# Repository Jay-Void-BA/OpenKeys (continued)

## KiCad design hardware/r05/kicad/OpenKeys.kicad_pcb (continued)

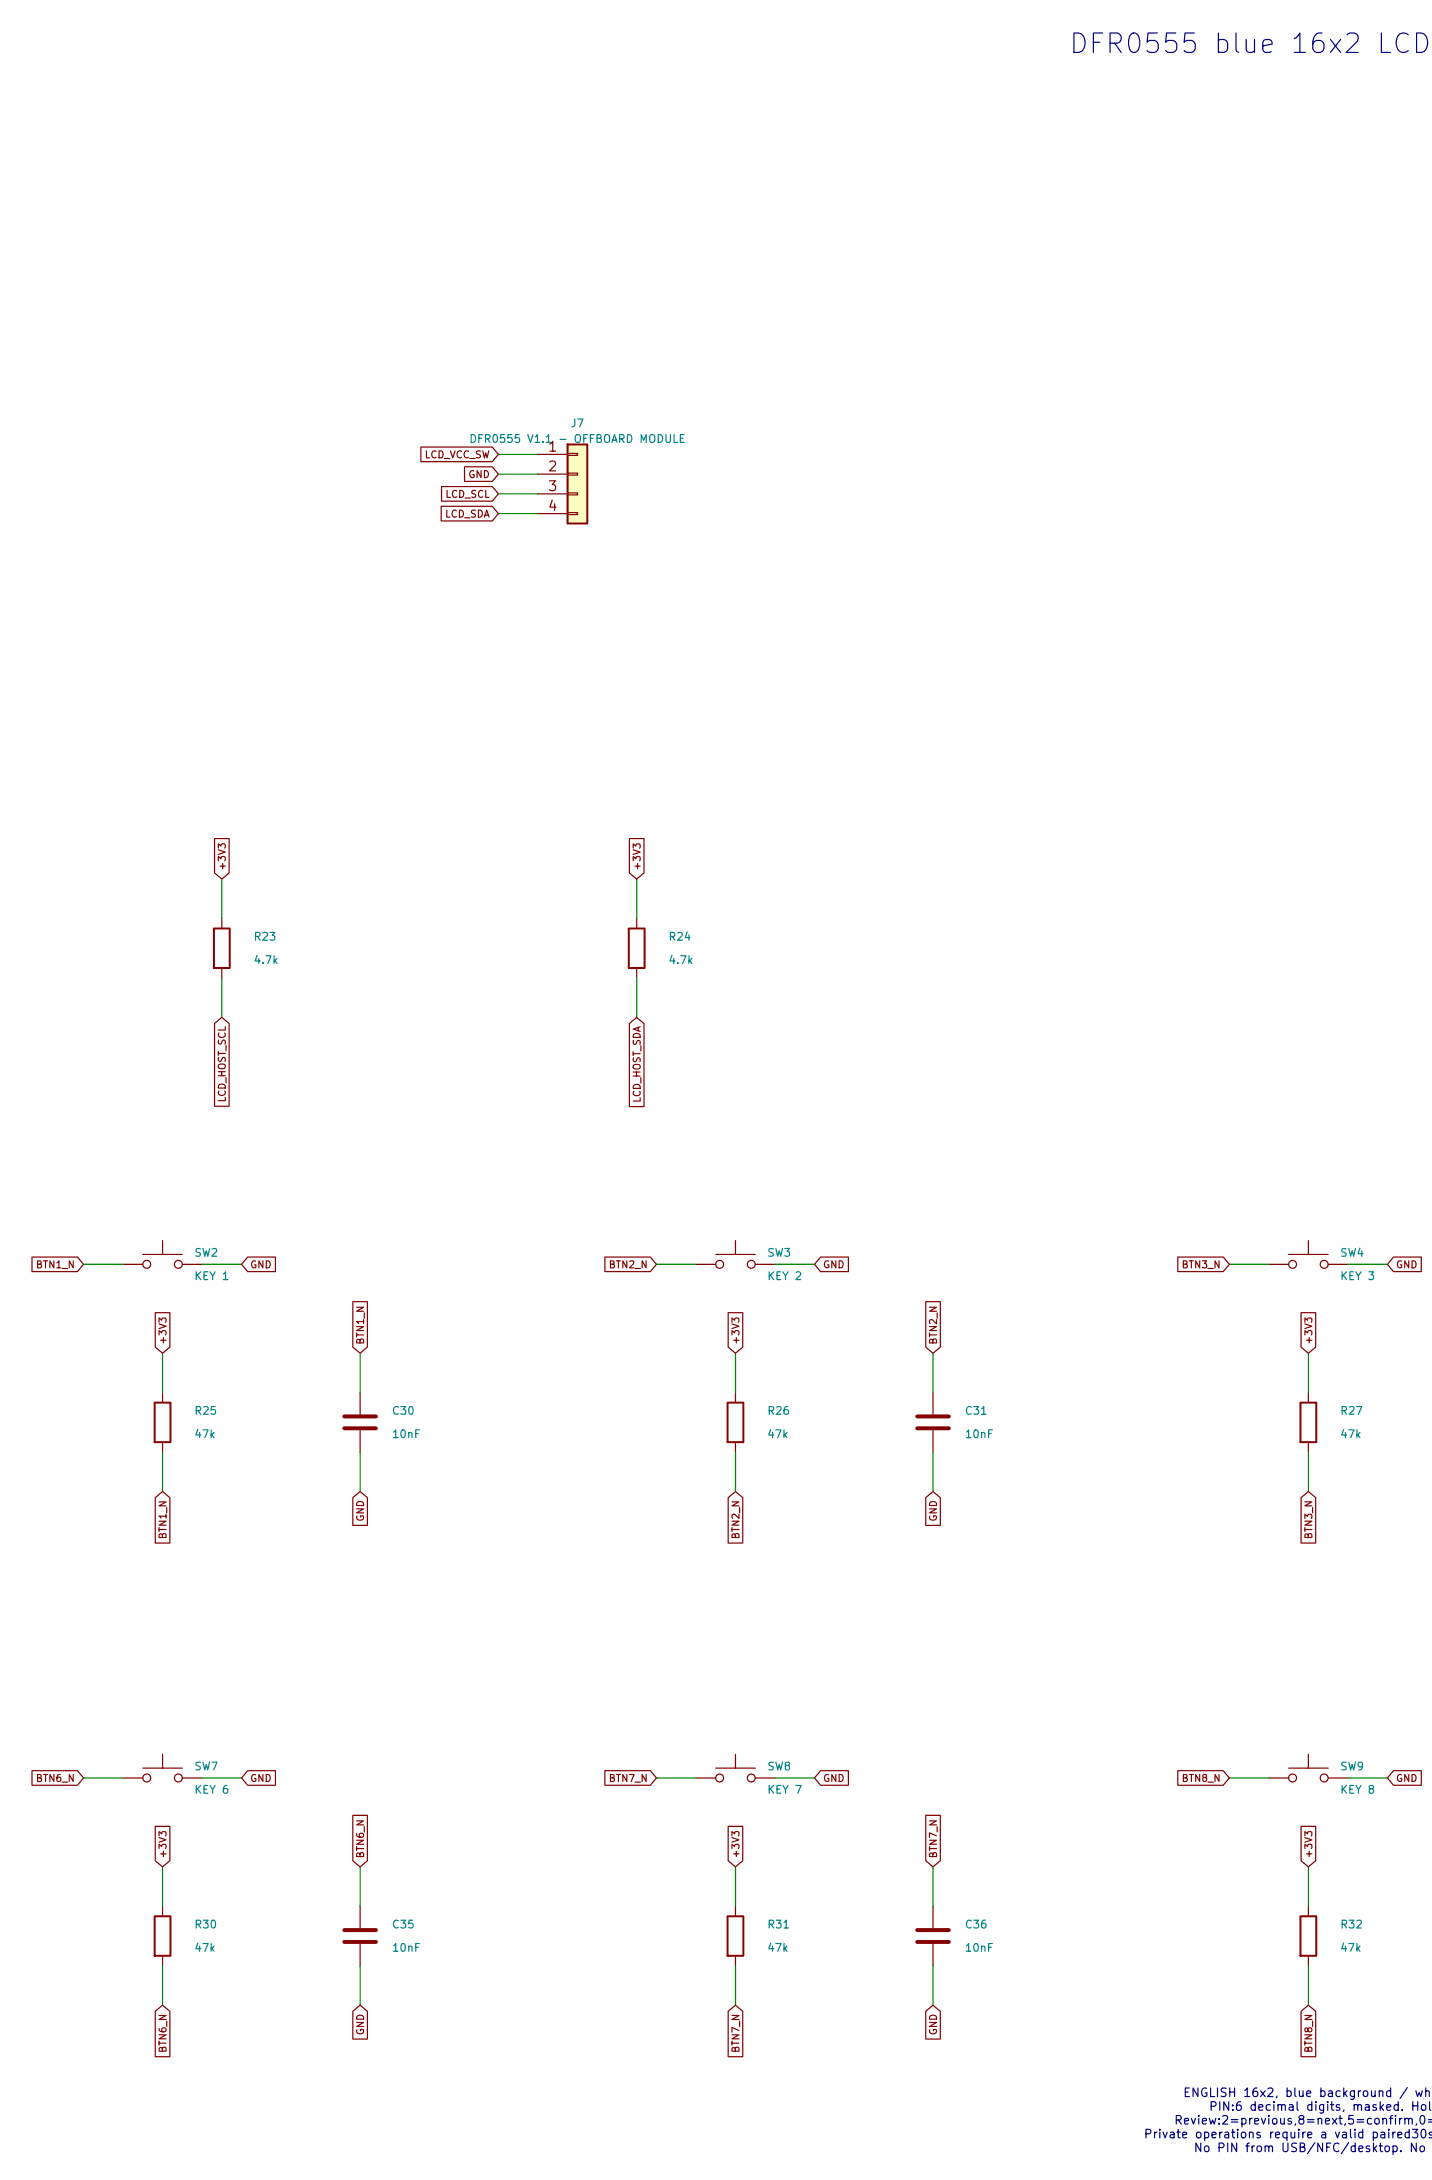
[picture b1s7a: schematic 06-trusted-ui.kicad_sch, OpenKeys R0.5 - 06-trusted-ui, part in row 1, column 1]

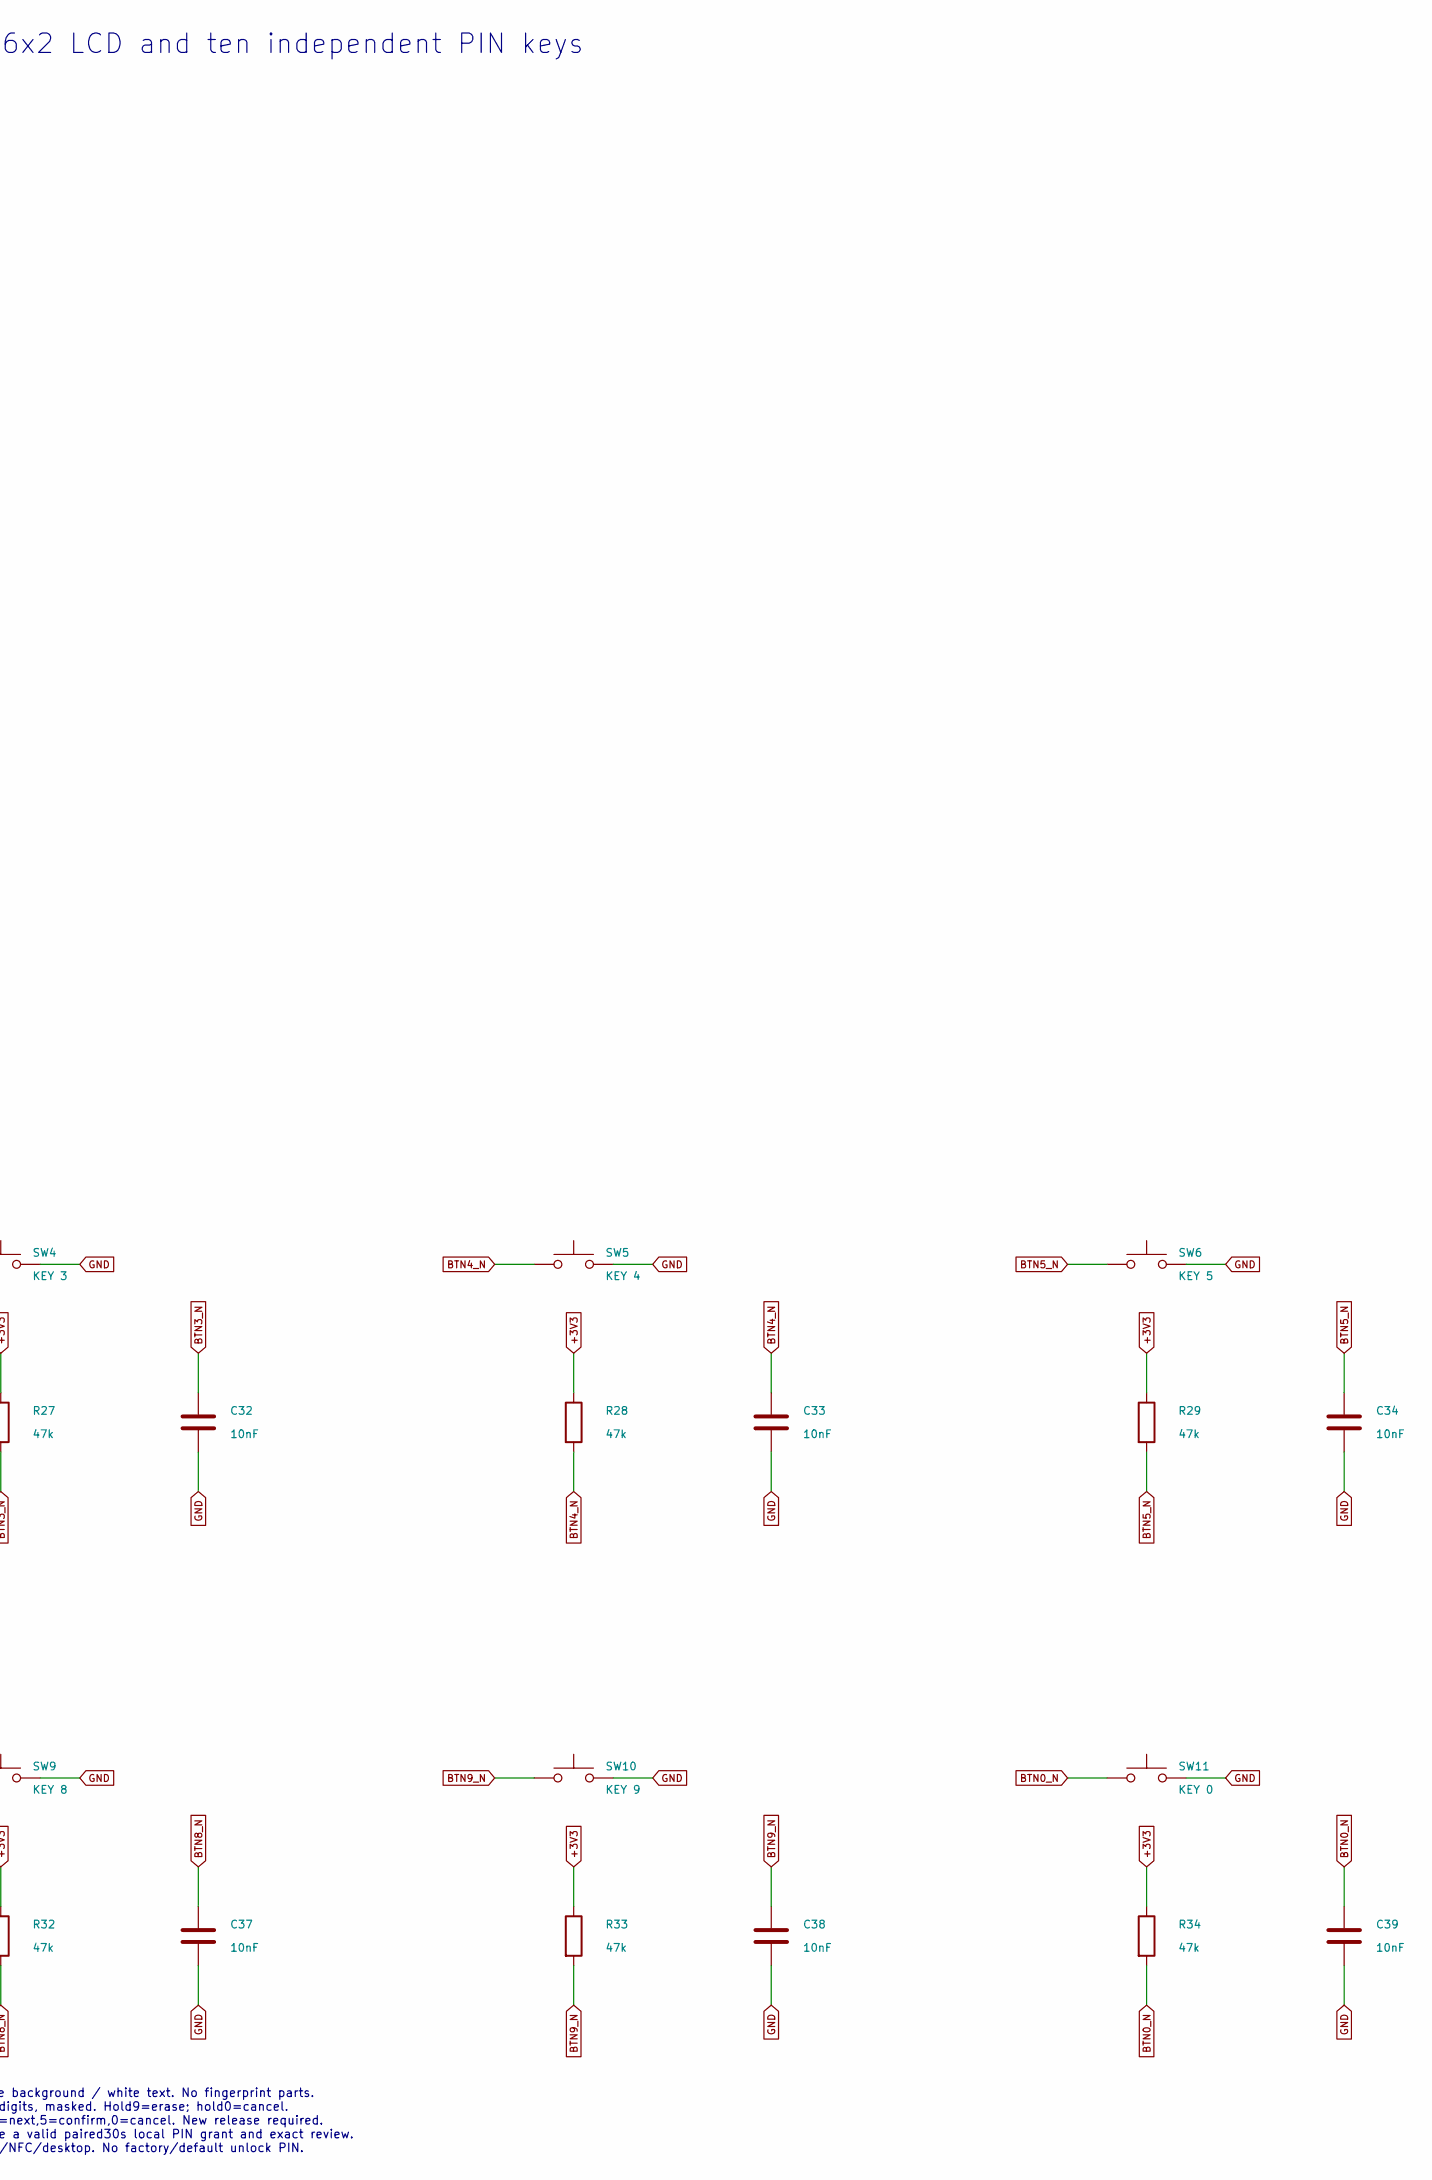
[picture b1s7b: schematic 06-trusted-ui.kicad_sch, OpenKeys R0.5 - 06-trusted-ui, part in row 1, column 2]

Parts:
C30, C31, C32, C33, C34, C35, C36, C37, C38, C39: 10nF; C_0603_1608Metric
J7: DFR0555 V1.1 - OFFBOARD MODULE; PinHeader_1x04_P2.54mm_Vertical
R23, R24: 4.7k; R_0603_1608Metric
R25, R26, R27, R28, R29, R30, R31, R32, R33, R34: 47k; R_0603_1608Metric
SW2: KEY 1; SW_SPST_TL3342
SW3: KEY 2; SW_SPST_TL3342
SW4: KEY 3; SW_SPST_TL3342
SW5: KEY 4; SW_SPST_TL3342
SW6: KEY 5; SW_SPST_TL3342
SW7: KEY 6; SW_SPST_TL3342
SW8: KEY 7; SW_SPST_TL3342
SW9: KEY 8; SW_SPST_TL3342
SW10: KEY 9; SW_SPST_TL3342
SW11: KEY 0; SW_SPST_TL3342

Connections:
+3V3: R23.1, R24.1, R25.1, R26.1, R27.1, R28.1, R29.1, R30.1, R31.1, R32.1, R33.1, R34.1; also elsewhere on the board
BTN0_N: C39.1, R34.2, SW11.1; also elsewhere on the board
BTN1_N: C30.1, R25.2, SW2.1; also elsewhere on the board
BTN2_N: C31.1, R26.2, SW3.1; also elsewhere on the board
BTN3_N: C32.1, R27.2, SW4.1; also elsewhere on the board
BTN4_N: C33.1, R28.2, SW5.1; also elsewhere on the board
BTN5_N: C34.1, R29.2, SW6.1; also elsewhere on the board
BTN6_N: C35.1, R30.2, SW7.1; also elsewhere on the board
BTN7_N: C36.1, R31.2, SW8.1; also elsewhere on the board
BTN8_N: C37.1, R32.2, SW9.1; also elsewhere on the board
BTN9_N: C38.1, R33.2, SW10.1; also elsewhere on the board
GND: C30.2, C31.2, C32.2, C33.2, C34.2, C35.2, C36.2, C37.2, C38.2, C39.2, J7.2, SW2.2, SW3.2, SW4.2, SW5.2, SW6.2, SW7.2, SW8.2, SW9.2, SW10.2, SW11.2; also elsewhere on the board
LCD_HOST_SCL: R23.2; also elsewhere on the board
LCD_HOST_SDA: R24.2; also elsewhere on the board
LCD_SCL: J7.3; also elsewhere on the board
LCD_SDA: J7.4; also elsewhere on the board
LCD_VCC_SW: J7.1; also elsewhere on the board

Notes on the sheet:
DFR0555 blue 16x2 LCD and ten independent PIN keys
ENGLISH 16x2, blue background / white text. No fingerprint parts. PIN:6 decimal digits, masked. Hold9=erase; hold0=cancel. Review:2=previous,8=next,5=confirm,0=cancel. New release required. Private operations require a valid paired30s local PIN grant and exact review. No PIN from USB/NFC/desktop. N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

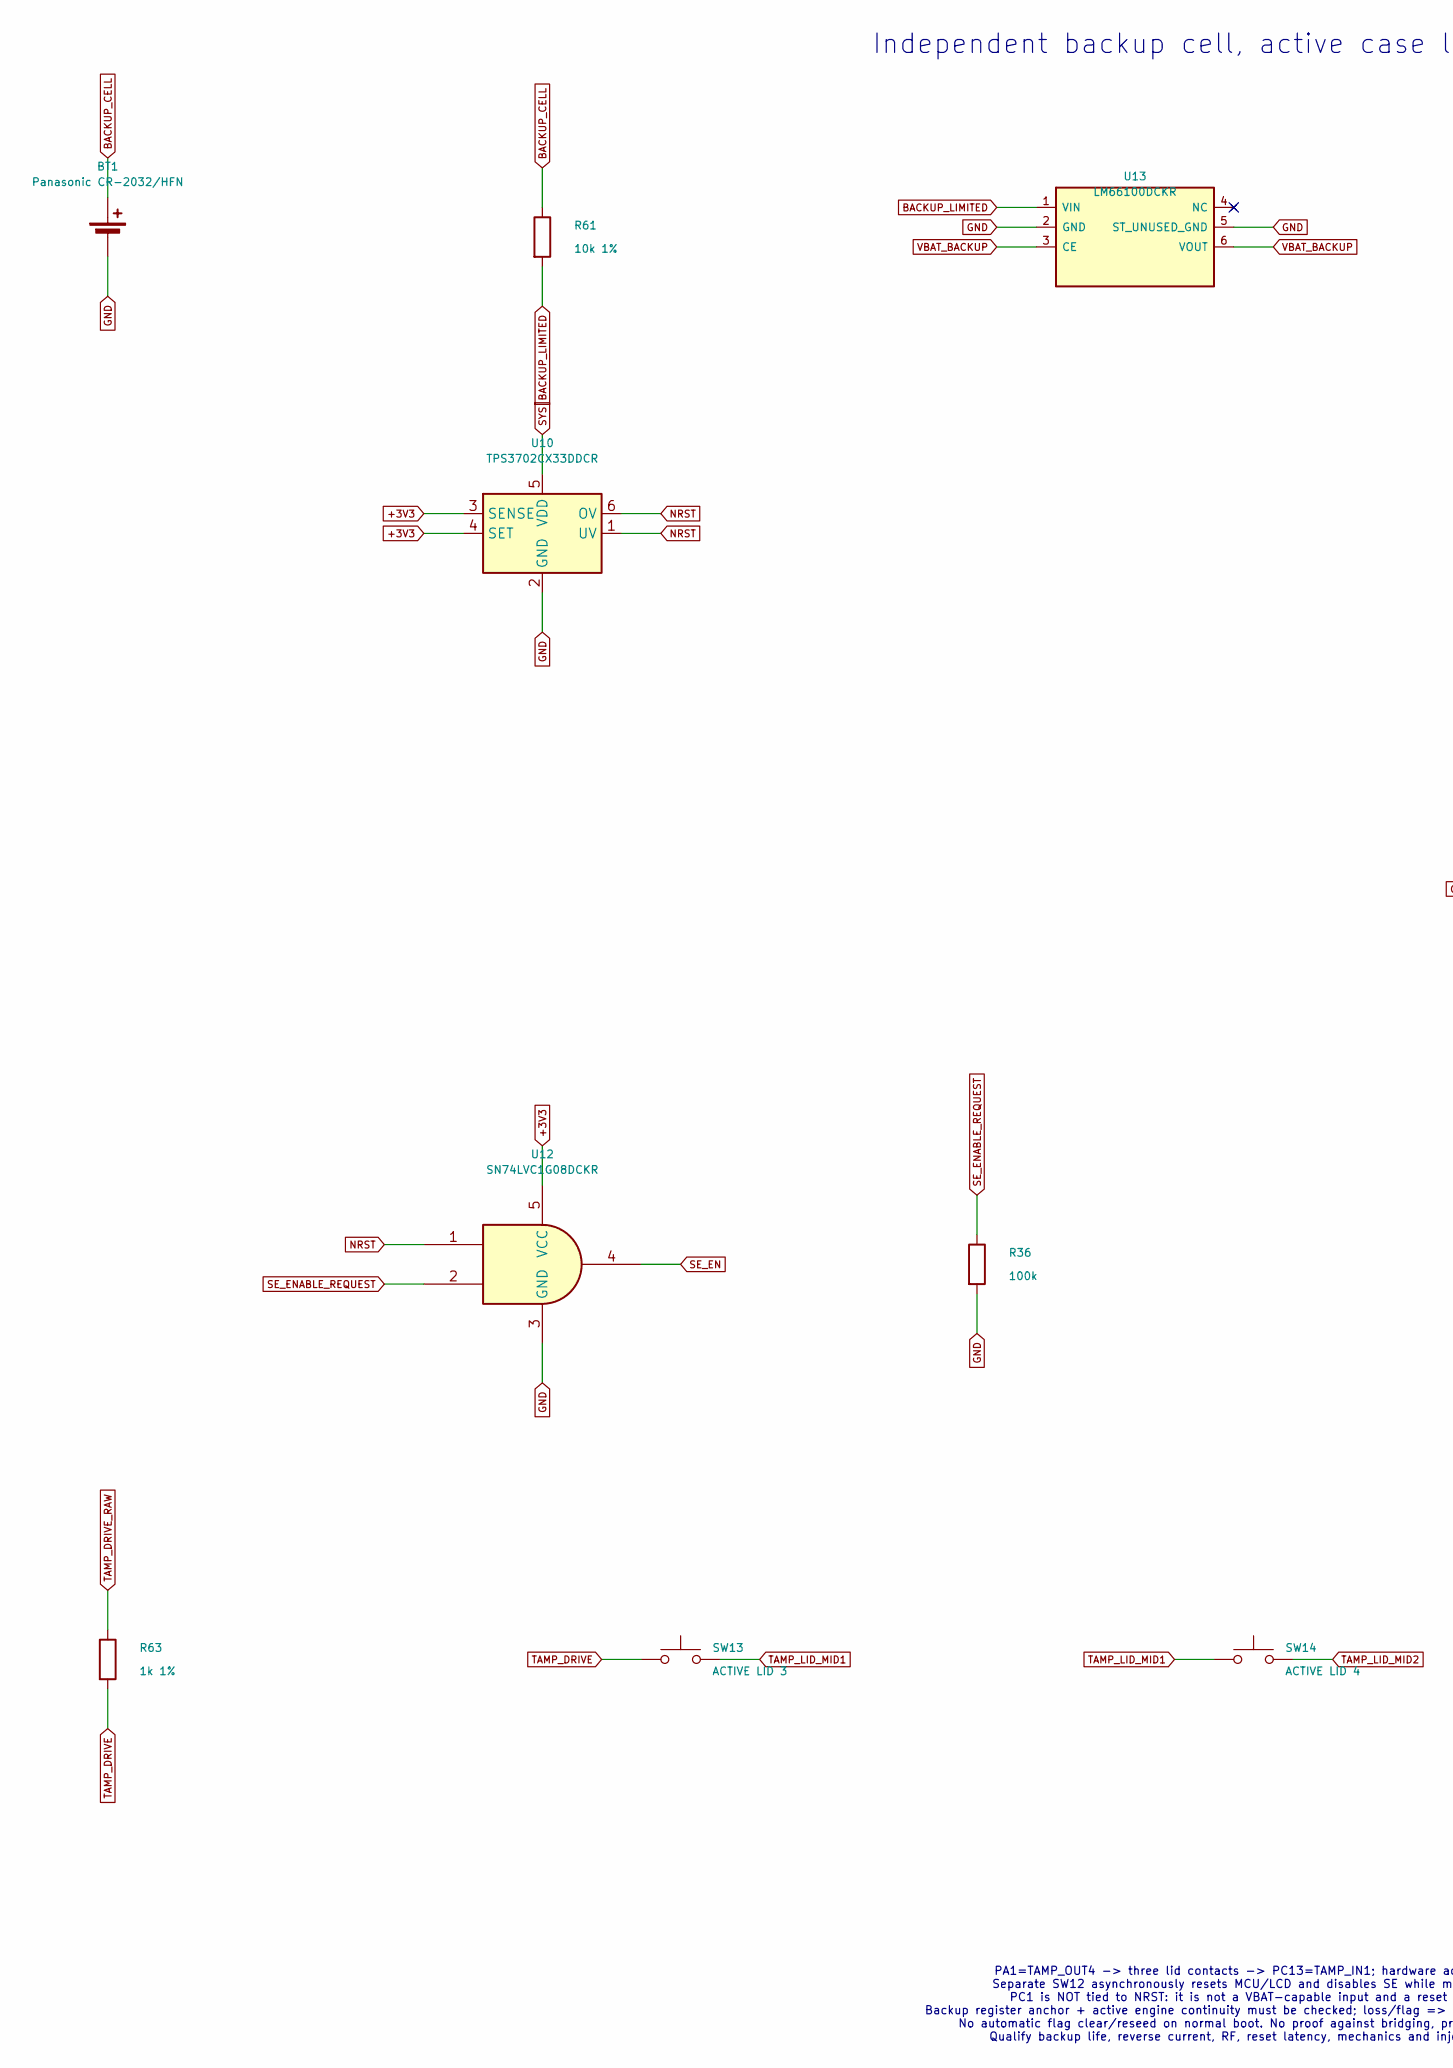
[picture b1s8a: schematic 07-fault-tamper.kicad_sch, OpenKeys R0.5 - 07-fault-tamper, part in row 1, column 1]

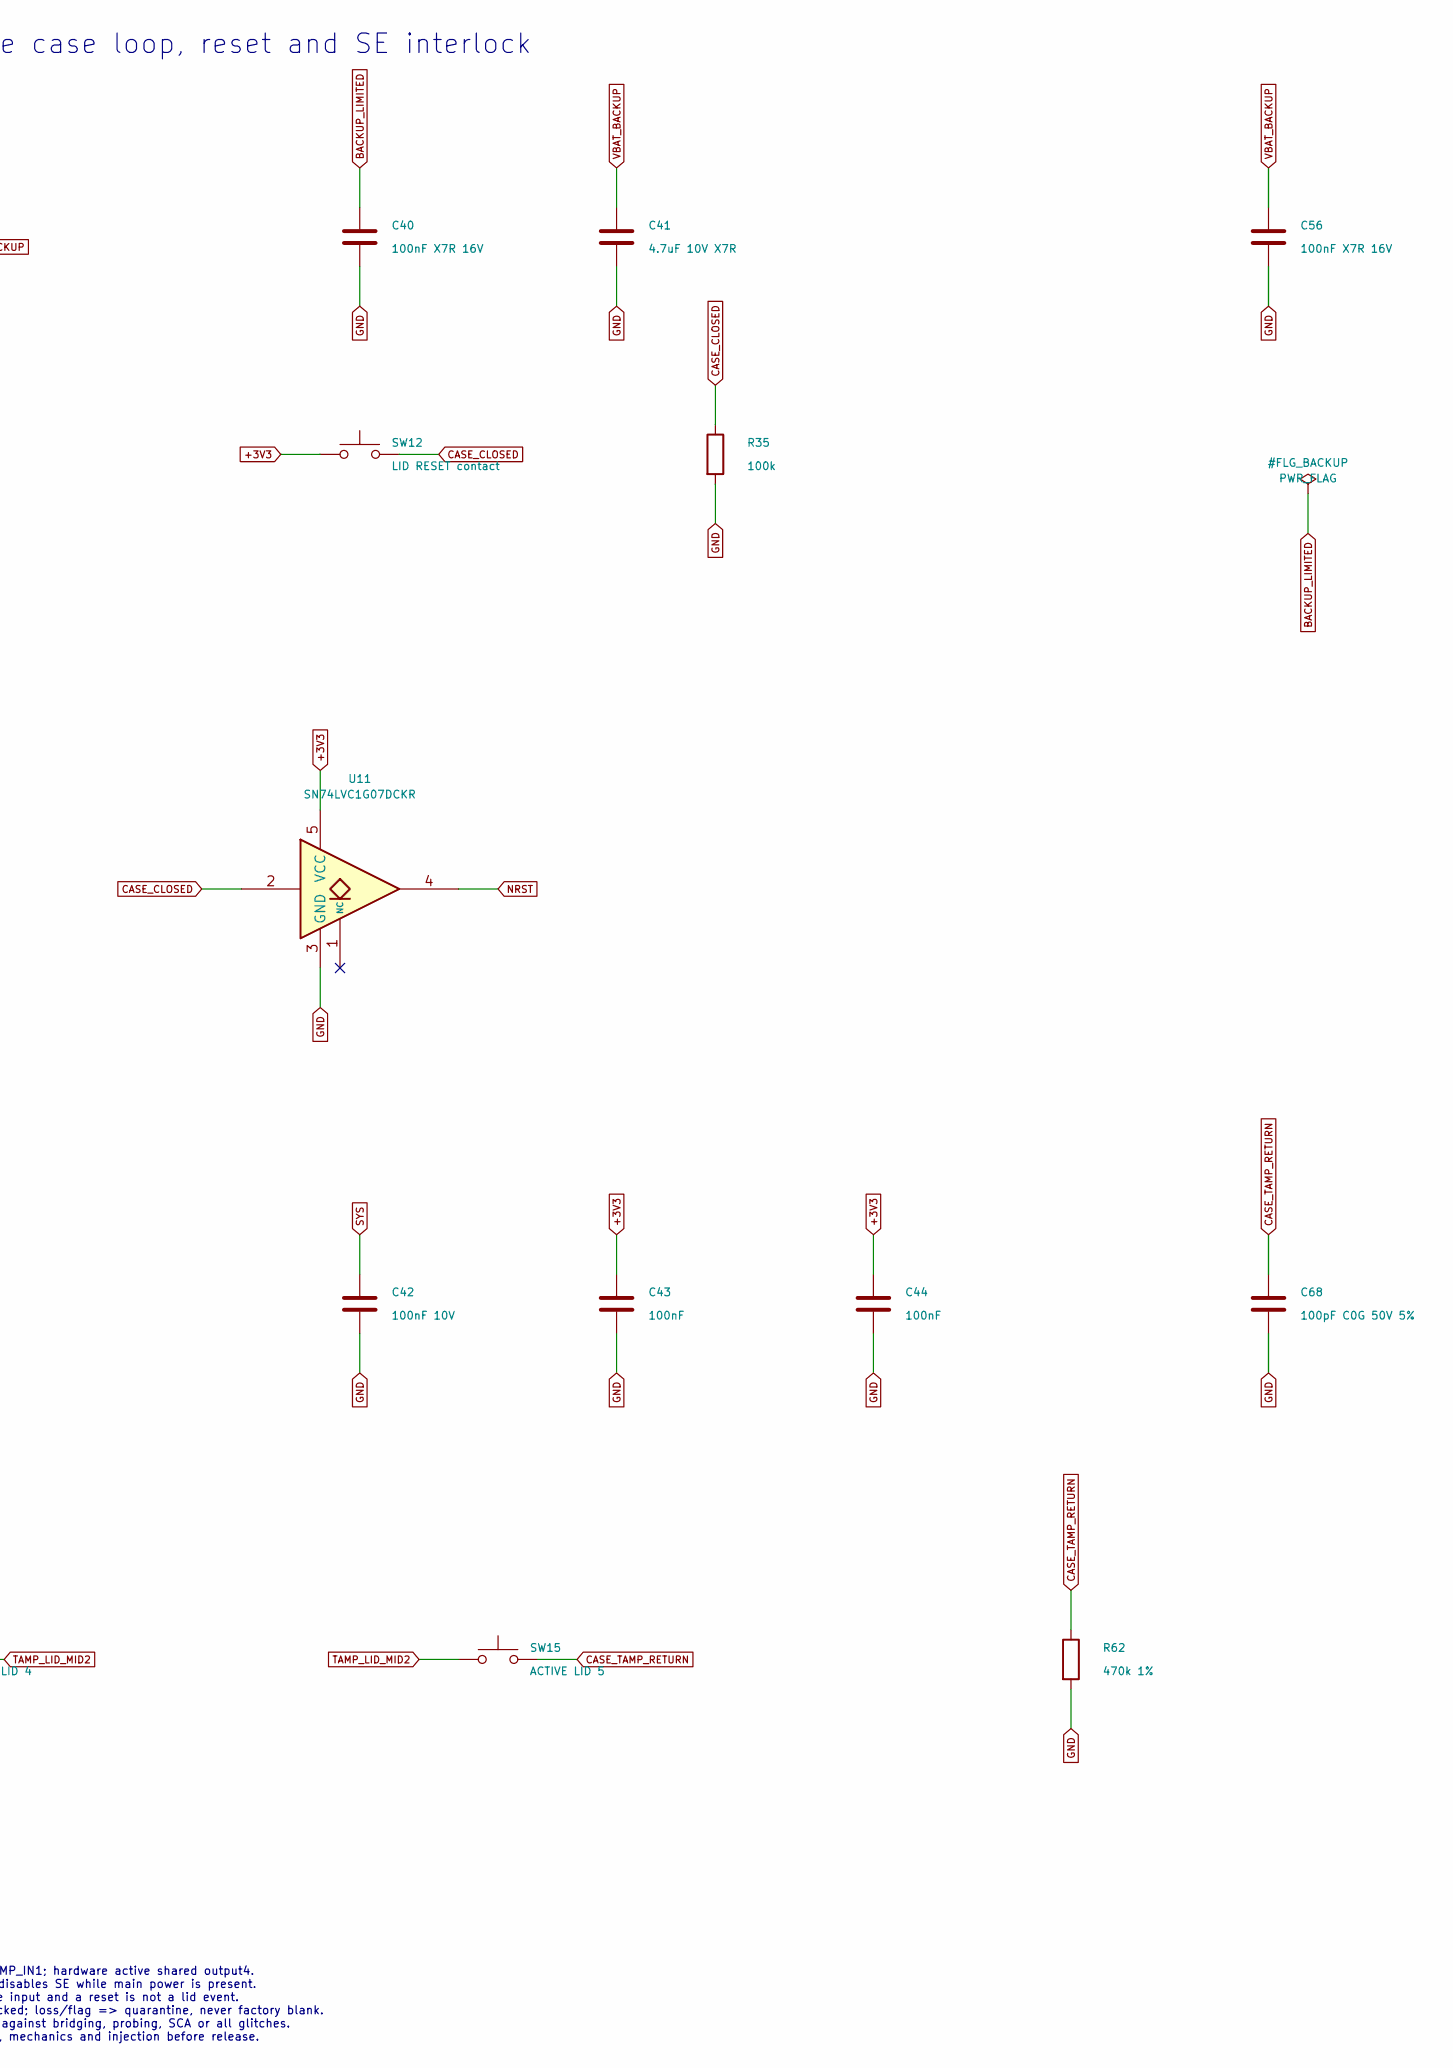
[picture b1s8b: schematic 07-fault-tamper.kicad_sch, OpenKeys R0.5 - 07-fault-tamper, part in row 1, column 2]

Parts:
BT1: Panasonic CR-2032/HFN; Battery_Panasonic_CR2032-HFN_Horizontal_CircularHoles
C40, C56: 100nF X7R 16V; C_0603_1608Metric
C41: 4.7uF 10V X7R; C_0805_2012Metric
C42: 100nF 10V; C_0603_1608Metric
C43, C44: 100nF; C_0603_1608Metric
C68: 100pF C0G 50V 5%; C_0603_1608Metric
R35, R36: 100k; R_0603_1608Metric
R61: 10k 1%; R_0603_1608Metric
R62: 470k 1%; R_0603_1608Metric
R63: 1k 1%; R_0603_1608Metric
SW12: LID RESET contact; SW_SPST_TL3342
SW13: ACTIVE LID 3; SW_SPST_TL3342
SW14: ACTIVE LID 4; SW_SPST_TL3342
SW15: ACTIVE LID 5; SW_SPST_TL3342
U10: TPS3702CX33DDCR; TSOT-23-6
U11: SN74LVC1G07DCKR; SOT-353_SC-70-5
U12: SN74LVC1G08DCKR; SOT-353_SC-70-5
U13: LM66100DCKR; SOT-363_SC-70-6

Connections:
+3V3: C43.1, C44.1, SW12.1, U10.3 (SENSE), U10.4 (SET), U11.5 (VCC), U12.5 (VCC); also elsewhere on the board
BACKUP_CELL: BT1.1 (+), R61.1
BACKUP_LIMITED: C40.1, R61.2, U13.1 (VIN)
CASE_CLOSED: R35.1, SW12.2, U11.2
CASE_TAMP_RETURN: C68.1, R62.1, SW15.2; also elsewhere on the board
GND: BT1.2 (-), C40.2, C41.2, C42.2, C43.2, C44.2, C56.2, C68.2, R35.2, R36.2, R62.2, U10.2 (GND), U11.3 (GND), U12.3 (GND), U13.2 (GND), U13.5 (ST_UNUSED_GND); also elsewhere on the board
NRST: U10.1 (UV), U10.6 (OV), U11.4, U12.1; also elsewhere on the board
SE_EN: U12.4; also elsewhere on the board
SE_ENABLE_REQUEST: R36.1, U12.2; also elsewhere on the board
SYS: C42.1, U10.5 (VDD); also elsewhere on the board
TAMP_DRIVE: R63.2, SW13.1
TAMP_DRIVE_RAW: R63.1; also elsewhere on the board
TAMP_LID_MID1: SW13.2, SW14.1
TAMP_LID_MID2: SW14.2, SW15.1
VBAT_BACKUP: C41.1, C56.1, U13.3 (CE), U13.6 (VOUT); also elsewhere on the board

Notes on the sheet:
Independent backup cell, active case loop, reset and SE interlock
PA1=TAMP_OUT4 -> three lid contacts -> PC13=TAMP_IN1; hardware active shared output4. Separate SW12 asynchronously resets MCU/LCD and disables SE while main power is present. PC1 is NOT tied to NRST: it is not a VBAT-capable input and a reset is not a lid event. Backup register anchor + active engi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

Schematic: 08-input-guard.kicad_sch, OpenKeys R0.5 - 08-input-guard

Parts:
C45: 100nF 50V; C_0603_1608Metric
C46: 1nF C0G; C_0603_1608Metric
D4: BZT52-C5V1,115; D_SOD-123
D5: SMF16A; D_SOD-123F
R37: 22.1k 1%; R_0603_1608Metric
R38: 10k 1%; R_0603_1608Metric
R39: 374k 0.1%; R_0603_1608Metric
R40: 100k 0.1%; R_0603_1608Metric
R41: 6.49k 1%; R_0603_1608Metric
R42: 47k; R_0603_1608Metric
U14: TPS259470LRPWR; TPS25947_RPW0010A

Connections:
+3V3: R42.1; also elsewhere on the board
GND: C45.2, C46.2, D4.2 (A), D5.2 (A2), R38.2, R40.2, R41.2, U14.8 (GND); also elsewhere on the board
USB_5V: U14.6 (OUT); also elsewhere on the board
USB_GUARD_DVDT: C46.1, U14.7 (DVDT)
USB_GUARD_EN: D4.1 (K), R37.2, R38.1, U14.1 (EN_UVLO)
USB_GUARD_FAULT_N: R42.2, U14.4 (FLT_N); also elsewhere on the board
USB_GUARD_ILM: R41.1, U14.9 (ILM)
USB_GUARD_OV: R39.2, R40.1, U14.2 (OVLO)
VBUS_FUSED: C45.1, D5.1 (A1), R37.1, R39.1, U14.5 (IN); also elsewhere on the board

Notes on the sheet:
Independent VBUS overvoltage cutoff, reverse blocking and limited inrush
OVLO nominal1.2V x(1+374k/100k)=5.688V. Component/leakage corners in protection-calculations.json. UVLO divider22.1k/10k: about3.85V nominal. EN is separately clamped, never raw VBUS. 6.49k ILM: about0.51A protection threshold; BQ charger still sets100mA input budget. 1nF DVDT: about2V/ms, about2.5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

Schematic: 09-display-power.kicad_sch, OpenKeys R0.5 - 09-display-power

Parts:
C47, C51, C52, C53, C54, C55: 100nF; C_0603_1608Metric
C48: 100nF 10% X7R 16V; C_0603_1608Metric
C49, C50: 1uF 10V; C_0805_2012Metric
R43: 10k; R_0603_1608Metric
R44, R45, R48: 100k; R_0603_1608Metric
R46: 220k 1%; R_0603_1608Metric
R47: 330R 1% 0.25W; R_1206_3216Metric
U15: SN74LVC1G07DCKR; SOT-353_SC-70-5
U16: SN74LVC1G74DCUR; VSSOP-8_2.3x2mm_P0.5mm
U17: TPS3808G33DBVR; SOT-23-6
U18: TPS22919DCKR; SOT-363_SC-70-6
U19: SN74LVC1G17DCKR; SOT-353_SC-70-5
U20: SN74LVC1G08DCKR; SOT-353_SC-70-5
U21: TCA9517ADGKR; VSSOP-8_3x3mm_P0.65mm

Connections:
+3V3: C47.1, C51.1, C52.1, C53.1, C54.1, C55.1, R43.1, U15.5 (VCC), U16.2 (D), U16.7 (PRE_N), U16.8 (VCC), U17.5 (SENSE), U17.6 (VDD), U19.5 (VCC), U20.5 (VCC), U21.1 (VCCA); also elsewhere on the board
BUS_ENABLE: R48.1, U20.4; also elsewhere on the board
CLEAR_N: U16.6 (CLR_N), U17.1 (RESET_N); also elsewhere on the board
CONNECT_DELAY: C48.1, R46.2, U19.2
DELAY_READY: U19.4, U20.2
GND: C47.2, C48.2, C49.2, C50.2, C51.2, C52.2, C53.2, C54.2, C55.2, R44.2, R45.2, R47.2, R48.2, U15.3 (GND), U16.4 (GND), U17.2 (GND), U18.2 (GND), U19.3 (GND), U20.3 (GND), U21.4 (GND); also elsewhere on the board
LCD_ARM_CLK: R45.1, U16.1 (CLK); also elsewhere on the board
LCD_BUFFER_EN: U21.5 (EN); also elsewhere on the board
LCD_HOST_SCL: U21.2 (SCLA); also elsewhere on the board
LCD_HOST_SDA: U21.3 (SDAA); also elsewhere on the board
LCD_RELEASE: R43.2, R44.1, U15.4, U17.3 (MR_N); also elsewhere on the board
LCD_RESET_CT: U17.4 (CT); also elsewhere on the board
LCD_SCL: U21.7 (SCLB); also elsewhere on the board
LCD_SDA: U21.6 (SDAB); also elsewhere on the board
LCD_VCC_SW: C50.1, R47.1, U18.5 (QOD), U18.6 (OUT), U21.8 (VCCB); also elsewhere on the board
NRST: U15.2; also elsewhere on the board
POWER_LATCH: R46.1, U16.5 (Q), U18.3 (ON), U20.1; also elsewhere on the board
SYS: C49.1, U18.1 (IN); also elsewhere on the board

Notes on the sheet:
Latched LCD power removal; isolated bus; no resetless retained text
U16 D=1, PRE_N=1. NRST/PC3 low clears Q through U17. CT through100k to VDD: RESET_N stays low180..420ms after MR release. Reset release alone does not restore LCD power; a NEW PC4 edge is required. Q controls TPS22919; Q AND delayed-Q drives U21 EN through U23 on sheet10. Lock: PC4 low, PC3 low, wa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

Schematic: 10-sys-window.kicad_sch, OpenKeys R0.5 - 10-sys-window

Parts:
C57, C58, C59: 100nF; C_0603_1608Metric
C60: 100nF X7R 16V 10%; C_0603_1608Metric
R49: 78.7k 0.1%; R_0603_1608Metric
R50, R52: 10k 0.1%; R_0603_1608Metric
R51: 110k 0.1%; R_0603_1608Metric
R53, R57, R59: 10k 1%; R_0603_1608Metric
R54, R58: 100k 1%; R_0603_1608Metric
R55, R56: 4.7k; R_0603_1608Metric
U22: TPS3700DDCR; TSOT-23-6
U23: SN74LVC1G07DCKR; SOT-353_SC-70-5

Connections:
+3V3: C58.1, C59.1, C60.1, R57.1, R58.1, U22.5 (VDD), U23.5 (VCC); also elsewhere on the board
BUS_ENABLE: U23.2; also elsewhere on the board
CLEAR_N: R57.2; also elsewhere on the board
GND: C57.2, C58.2, C59.2, C60.2, R50.2, R52.2, R54.2, R59.2, U22.2 (GND), U23.3 (GND); also elsewhere on the board
LCD_BUFFER_EN: R53.2, R54.1, U23.4; also elsewhere on the board
LCD_RESET_CT: R58.2; also elsewhere on the board
LCD_SCL: R55.2; also elsewhere on the board
LCD_SDA: R56.2; also elsewhere on the board
LCD_VCC_SW: C57.1, R53.1, R55.1, R56.1; also elsewhere on the board
NRST: U22.1 (OUTA), U22.6 (OUTB); also elsewhere on the board
POWER_LATCH: R59.1; also elsewhere on the board
SYS: R49.1, R51.1; also elsewhere on the board
SYS_OV_SENSE: R51.2, R52.1, U22.4 (INB-)
SYS_UV_SENSE: R49.2, R50.1, U22.3 (INA+)

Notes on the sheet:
SYS voltage window and LCD level-buffer fail-closed enable
TPS3700 reference: positive396..404mV; negative387..400mV. Include0.1percent divider errors and +/-25nA input bias. Static SYS UV fall min3.4246V; OV rise max4.8596V. With ASSUMED switch+harness drop<=50mV: LCD>=3.3746V. Main3.3V fixed PWM:3.267..3.333V; no ripple/transient guarantee. TCA sideA=mai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

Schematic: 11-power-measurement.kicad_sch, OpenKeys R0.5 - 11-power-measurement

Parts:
C61: 10nF X7R 16V; C_0603_1608Metric
C67: 100nF X7R 16V; C_0603_1608Metric
R64, R65: 330k 1%; R_0603_1608Metric
R68: 100k 1%; R_0603_1608Metric
U28: TMUX1511RWBR; Texas_X2QFN-12_1.6x1.6mm_P0.4mm

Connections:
+3V3: C67.1, U28.2 (VDD); also elsewhere on the board
BAT: R64.1; also elsewhere on the board
BATTERY_DIVIDER: C61.1, R64.2, R65.1, U28.3 (S1)
BATTERY_SENSE: R68.1, U28.4 (D1); also elsewhere on the board
GND: C61.2, C67.2, R65.2, R68.2, U28.1 (GND), U28.5 (S2), U28.6 (D2), U28.8 (SEL2), U28.9 (D4), U28.10 (S4), U28.11 (D3), U28.12 (S3); also elsewhere on the board
NRST: U28.7 (SEL1); also elsewhere on the board

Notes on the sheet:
Protected main-cell voltage measurement; no invented battery percentage
PA0=ADC1_INP0 analog only. Read VREFINT/calibration; use long sample time and settled bounded samples. 330k/330k divider +100k output bias: nominal Vadc/Vbat=100/530 when U28 is on. Reservoir is upstream of U28. NRST low disconnects ADC; powered-off path must not backfeed main rail. Voltage/chargin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

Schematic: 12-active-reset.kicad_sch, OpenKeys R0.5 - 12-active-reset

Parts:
C62: 10nF X7R 16V 10%; C_0603_1608Metric
C63, C64, C65, C66: 100nF X7R 16V; C_0603_1608Metric
R66: 4.7k 1%; R_0603_1608Metric
R67: 1M 1%; R_0603_1608Metric
R69: 9.1k 1%; R_0603_1608Metric
U24: SN74AUP1G99DCUR; VSSOP-8_2.3x2mm_P0.5mm
U25: SN74LVC1G14DCKR; SOT-353_SC-70-5
U26: SN74LVC1G07DCKR; SOT-353_SC-70-5
U27: SN74AUP2G17DCKR; SOT-363_SC-70-6

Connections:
+3V3: C63.1, C64.1, C65.1, C66.1, R69.1, U24.3 (B), U24.8 (VCC), U25.5 (VCC), U26.5 (VCC), U27.5 (VCC); also elsewhere on the board
CASE_TAMP_RETURN: U27.3 (2A); also elsewhere on the board
GND: C62.2, C63.2, C64.2, C65.2, C66.2, R67.2, R69.2, U24.1 (OE_N), U24.2 (A), U24.4 (GND), U25.3 (GND), U26.3 (GND), U27.2 (GND); also elsewhere on the board
NRST: U26.4; also elsewhere on the board
TAMP_DIFF: R66.1, U24.7 (Y)
TAMP_DIFF_FILTER: C62.1, R66.2, U25.2
TAMP_DRIVE_CLEAN: U24.5 (C), U27.6 (1Y)
TAMP_DRIVE_RAW: R67.1, U27.1 (1A); also elsewhere on the board
TAMP_MATCH_N: U25.4, U26.2
TAMP_RETURN_CLEAN: U24.6 (D), U27.4 (2Y)

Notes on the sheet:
Independent active-loop mismatch reset; no software arm or override
Closed loop: C=D => no reset. Open/stuck/grounded loop: mismatch pulses feed RC and hard reset. U24 OE and function straps are fixed copper, not GPIO. No host bypass or software mask. U27 Ioff limits feed into unpowered main logic; leakage is not zero. No maximum input slew at U27/U25. Active TAMP 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

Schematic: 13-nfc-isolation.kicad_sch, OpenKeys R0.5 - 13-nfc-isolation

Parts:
C69, C70, C71: 100nF X7R 16V; C_0603_1608Metric
R70, R71, R72, R73, R74: 330R 1%; R_0603_1608Metric
R75, R76, R77: 100k 1%; R_0603_1608Metric
U29, U30: TMUX1511RWBR; Texas_X2QFN-12_1.6x1.6mm_P0.4mm
U31: LM66100DCKR; SOT-363_SC-70-6

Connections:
+3V3: C69.1, C70.1, C71.1, U29.2 (VDD), U30.2 (VDD), U31.1 (VIN); also elsewhere on the board
GND: C69.2, C70.2, C71.2, R76.2, R77.2, U29.1 (GND), U30.1 (GND), U30.5 (S2), U30.6 (D2), U30.9 (D4), U30.10 (S4), U30.11 (D3), U30.12 (S3), U31.2 (GND), U31.5 (ST_UNUSED_GND); also elsewhere on the board
NFC_CS_ISO: R70.1, U29.4 (D1)
NFC_CS_N: U29.3 (S1); also elsewhere on the board
NFC_IRQ_ISO: R74.1, U30.4 (D1)
NFC_IRQ_N: U30.3 (S1); also elsewhere on the board
NFC_MISO: U29.10 (S4); also elsewhere on the board
NFC_MISO_ISO: R73.1, U29.9 (D4)
NFC_MOSI: U29.12 (S3); also elsewhere on the board
NFC_MOSI_ISO: R72.1, U29.11 (D3)
NFC_RF_CS_N: R70.2, R75.2; also elsewhere on the board
NFC_RF_IRQ_N: R74.2; also elsewhere on the board
NFC_RF_MISO: R73.2; also elsewhere on the board
NFC_RF_MOSI: R72.2, R77.1; also elsewhere on the board
NFC_RF_SCK: R71.2, R76.1; also elsewhere on the board
NFC_SCK: U29.5 (S2); also elsewhere on the board
NFC_SCK_ISO: R71.1, U29.6 (D2)
NFC_VCC: R75.1, U31.3 (CE), U31.6 (VOUT); also elsewhere on the board
NRST: U29.7 (SEL1), U29.8 (SEL2), U30.7 (SEL1), U30.8 (SEL2); also elsewhere on the board

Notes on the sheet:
NFC RF domain - physical SPI/IRQ isolation and VCC reverse blocking
RF can power U7 while main3.3V is absent. VOUT isolation alone does not bound signal backfeed. Five TMUX1511 channels interrupt CS/SCK/MOSI/MISO/IRQ on reset and main-power loss. Host pullups remain main-side; RF-side CS high and SCK/MOSI low have local passive defaults. The3.6V off-terminal rating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
